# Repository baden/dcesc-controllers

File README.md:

# dcesc-controllers

Тут буде і плата і програма.

## Так. Шось в процесі ми якось дішли до потужної плати. І назва трохи не відповідає.

## Мотори

Експериментую з моторами з редуктором.

Починаю експерімент з [JGA25-370](https://www.aliexpress.com/item/1005006961499514.html)
та [GA24Y-370](https://www.aliexpress.com/item/1005005835525169.html)

на двигунах діаметром 24.4мм

Ціль:
напруга живлення - 24В
струм - 3А
керування - RS485

Хотілось би CAN, але поки не підібрани варіанти конролера.

Пропонується варіанти драйвера двигуна:

- [DRV8870DDAR](https://www.kosmodrom.ua/mikroshema-kontrolera-dviguna/drv8870ddar-4.html) - 12грн
- [DRV8874PWPR](https://www.kosmodrom.ua/mikroshema-kontrolera-dviguna/drv8874pwpr-2.html) - 44грн

# Робимо цю версію на готових драйверах. Бо два-три мотори на одному мікроконтроллері то дуже складно.

## На майбутньє, може буду підбирати якісь китайські компоненти, бо ціна на амеріканських брендах виходить якась зовсім неадекватна.

## Встановлення інструментів

https://github.com/riscv-software-src/homebrew-riscv

```bash
brew tap riscv-software-src/riscv
brew install riscv-tools
brew install riscv-openocd
brew test riscv-tools
/opt/homebrew/opt/riscv-gnu-toolchain/bin/riscv64-unknown-elf-gcc --version
```

/opt/homebrew/opt/riscv-openocd/bin/openocd

## Обираємо мікроконтролер

Я ще не визначився, чи треба робити виключно на CAN, чи може обійтись RS485.

- Оцей мабуть ідеальний для контролеру двигуна
https://www.kosmodrom.ua/mikrokontroler/stm32g431cbt6.html

Для плат с готовий драйвером двигуна, контролер:

https://www.kosmodrom.ua/mikrokontroler/stm32f042f6p6.html

- Шось мегапопулярне, але не впевнен шо воно.
https://www.kosmodrom.ua/mikrokontroler/stm32f103c8t6.html

- Ексотіка для ізвращьєнців
https://www.kosmodrom.ua/mikrokontroler/gd32f103cbt6-2.html

Ще подивлюсь на цей: CH32V203. Здається є сумісний по ногам як STM, так і GD, так і AT

## Обираємо транзистор на потужну плату

### 60 V

https://www.kosmodrom.ua/tranzistor-poloviy-mosfet/60n06-2.html, 39 nC, 14mOhm
https://www.kosmodrom.ua/tranzistor-poloviy-mosfet/csd18537nq5a-2.html, 18 nC, 13mOhm
https://www.kosmodrom.ua/tranzistor-poloviy-mosfet/aon7262e-2.html, 45 nC, 6.2mOhm

## Драйвер MOSFET

https://www.kosmodrom.ua/drayveri-igbt-mosfet/eg3013s-2.html, 0.8/1.0A,

## Драйвер CAN-шини.

Треба або взяти 3.3В CAN, ти живити окремим живленням 5V, та обирати з Vio, чи согласовувати рівні.

https://www.kosmodrom.ua/interfeys-can-2/sn65hvd230dr.html
https://www.kosmodrom.ua/interfeys-can-2/sn65hvd232d.html (no stb and sleep)

## Готовий контролер на слабкіший мотор

https://www.kosmodrom.ua/mikroshema-kontrolera-dviguna/drv8870ddar-4.html, 3.6А, 45V
https://www.kosmodrom.ua/mikroshema-kontrolera-dviguna/drv8870ddar-2.html,
https://www.kosmodrom.ua/mikroshema-kontrolera-dviguna/drv8874pwpr-2.html, 6А, 37V

## Всіляке різне

https://www.kosmodrom.ua/tranzistor-poloviy-mosfet/ao4828.html, дешевий сдвоєний мосфет на драйвер до 3А.

https://www.kosmodrom.ua/stabilizator-naprugi/ht7533s-umw-2.html, Стабілізатор напруги на процесор, 3.3V, 0.1A

## Во, подивиться це

https://github.com/wagiminator/CH32V003-GameConsole/tree/main

Ще це:
https://github.com/wagiminator/MCU-Templates

Ще тут купа посилань:
https://github.com/wagiminator/Development-Boards/tree/main/CH32V003A4M6_DevBoard

https://github.com/AlessandroAU/ESP32-CRSF-Packet-Gen/blob/master/CRSF_testcode/CRSF.h
https://px4.github.io/Firmware-Doxygen/d9/dd2/crsf_8cpp_source.html

https://github.com/vedderb/bldc_uart_comm_stm32f4_discovery/blob/c19a6283e187040f25aa52e213673938db054d06/bldc_interface.c#L567

https://vedder.se/2015/10/communicating-with-the-vesc-using-uart/

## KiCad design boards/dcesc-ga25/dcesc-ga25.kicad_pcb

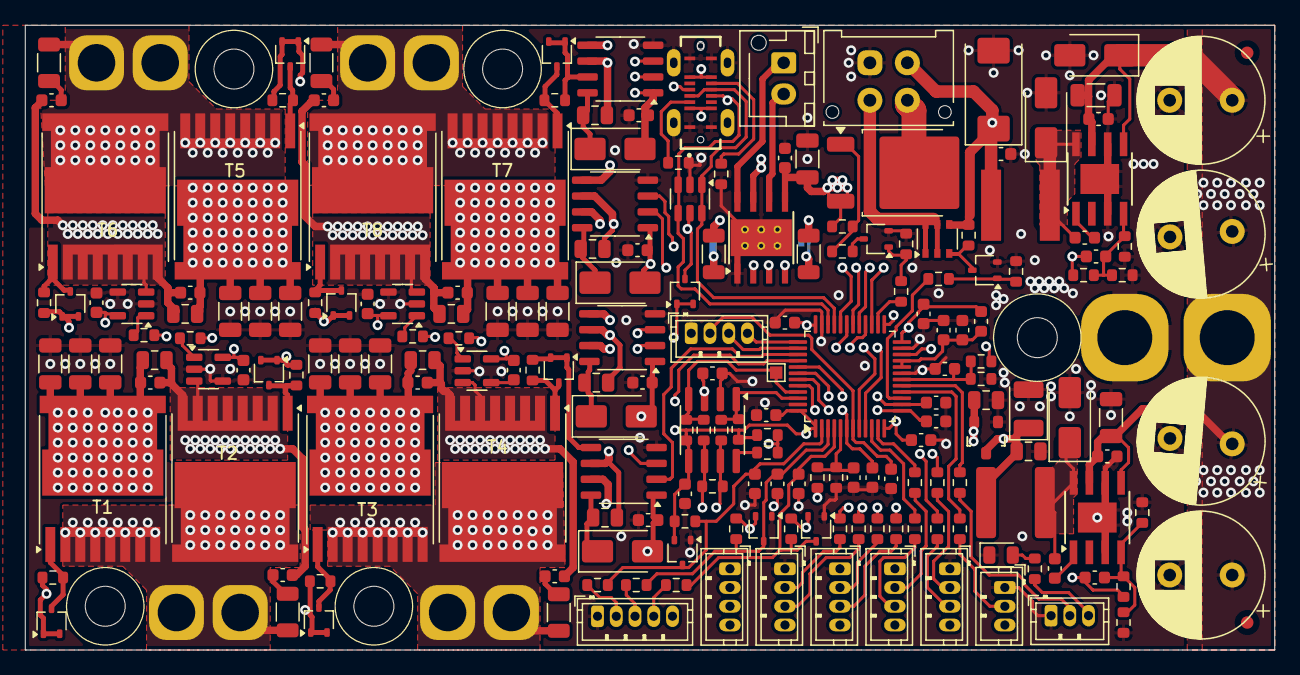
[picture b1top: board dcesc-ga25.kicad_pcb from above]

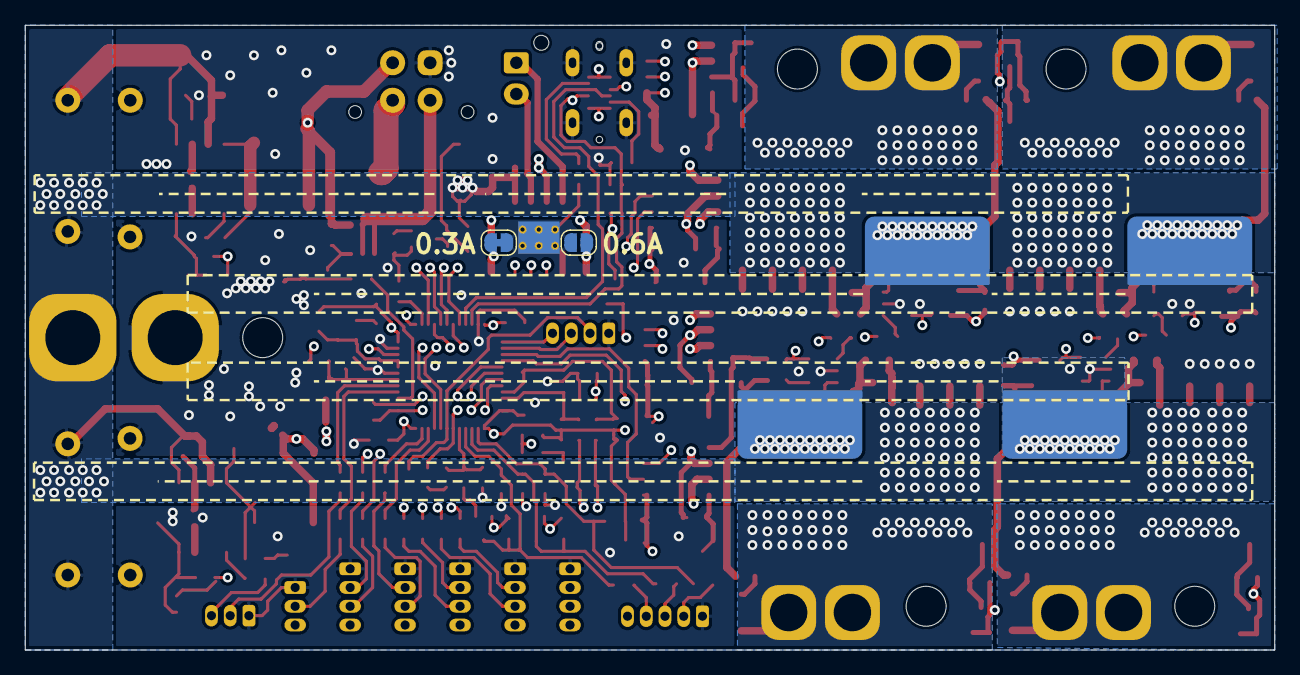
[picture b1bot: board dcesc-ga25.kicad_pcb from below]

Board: 4 copper layers, 100.0 x 50.0 mm, 219 parts (6 on the bottom side), 119 nets.

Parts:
C1, C2, C14, C53, C54, C55, C56, C57, C58, C59, C60, C61, C62, C63, C64: 10uF; C_1206_3216Metric
C3, C4, C5, C6, C10, C15, C16, C17, C18, C19, C20, C21, C25, C27, C28, C29, C30, C31, C32, C33, C34, C35, C36, C37, C38, C39, C40: 0.1uF; C_0603_1608Metric
C7, C8: 82p; C_0603_1608Metric
C9: 100uF; CP_EIA-7343-15_Kemet-W
C11: 100uF; CP_EIA-3528-12_Kemet-T
C12, C13, C45, C46, C47, C48: 10uF; C_0805_2012Metric
C22, C23, C24, C26: 10nF; C_0603_1608Metric
C41, C42, C43, C44: 33nF; C_0603_1608Metric
C49, C50, C51, C52: 1uF; C_0805_2012Metric
C65, C66, C67, C68: 220uF; CP_Radial_D10.0mm_P5.00mm
C69, C70, C71, C72: 3.3nF; C_0603_1608Metric
D1: SMAJ28A; D_SMA
D2, D3, D15, D16, D17, D18: SS24; D_SMA
D4, D5, D6: BAT54SW; SOT-323_SC-70
D7, D8, D9, D10, D11, D12, D13, D14, D19: BAT54AW; SOT-323_SC-70
D20: LED; LED_0805_2012Metric
FB1: FerriteBead; L_0603_1608Metric
FID1, FID2: Fiducial; Fiducial_1mm_Mask2mm
H1, H2, H3, H4, H5: MountingHole; MountingHole_3.2mm_M3
J1: Jumper_2_Open; SolderJumper-2_P1.3mm_Open_RoundedPad1.0x1.5mm
J2: Jumper_2_Bridged; SolderJumper-2_P1.3mm_Bridged_RoundedPad1.0x1.5mm
J3, J4, J5, J6, J7, J8, J9, J10: Conn_01x01_Socket; SolderWire-2.5sqmm_1x01_D2.4mm_OD4.4mm
J18, J19: Conn_01x01_Socket; SolderWire-6sqmm_1x01_D3.5mm_OD7mm
L1, L2: 10uH; Inductor_NR6028T100M
R1, R7, R8, R12, R13, R21, R36: 30k; R_0603_1608Metric
R2, R5, R57: 3.3k; R_0603_1608Metric
R3, R6, R9, R10, R11, R22, R23, R24, R42: 100k; R_0603_1608Metric
R4, R18, R19, R20: 10k; R_0603_1608Metric
R14: 0.51R; R_1206_3216Metric
R15: 1R; R_1206_3216Metric
R16: 120; R_0603_1608Metric
R17, R35: 330k; R_0603_1608Metric
R25, R26, R27, R28, R29, R30, R31, R32, R33, R34, R63, R64: 100; R_0603_1608Metric
R37, R38, R39, R40, R41: 1k; R_0603_1608Metric
R43, R44, R45, R46, R47, R48, R49, R50: 10; R_0603_1608Metric
R51, R52, R53, R54: 3; R_1206_3216Metric
R55, R56, R61, R62: 5.1k; R_0603_1608Metric
R57-1, R58-1, R59-1, R60-1: 0.2mOhm; R_SHUNT
T1, T2, T3, T4, T5, T6, T7, T8: IPT012N08N5; Infineon_PG-HSOF-8-1
T9, T10: BC847AW; SOT-323_SC-70
T11: IRF5803TRPBF; TSOP-6_1.65x3.05mm_P0.95mm
T12: AOD4185; TO-252-2
TP1: BOOT0; TestPoint_Pad_1.0x1.0mm
U1, U2: ST1S14PHR; TI_SO-PowerPAD-8
U3: MCP1703A-3302; MCP1703
U4: STM32G431C8Tx; LQFP-48_7x7mm_P0.5mm
U5, U6, U7, U8: INA180A4; SOT-23-5
U9, U10, U11, U12: EG3112; SOP-8_3.9x4.9mm_P1.27mm
U13: DRV8870DDA; Texas_HTSOP-8-1EP_3.9x4.9mm_P1.27mm_EP2.95x4.9mm_Mask2.4x3.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
U14: ATA6561-GAQW-N; SOIC-8_3.9x4.9mm_P1.27mm
U15: USBLC6-2SC6; SOT-23-6
X1: Conn_02x02_Top_Bottom; Molex_Micro-Fit_3.0_43045-0412_2x02_P3.00mm_Vertical
X2: Conn_01x03; JST_XH_B2B-XH-AM_1x02_P2.50mm_Vertical
X3, X4, X5, X6, X7, X11: Conn_01x03; JST_ZH_B4B-ZR_1x04_P1.50mm_Vertical
X8, X9: Conn_01x03; JST_ZH_B3B-ZR_1x03_P1.50mm_Vertical
X10: Conn_01x03; JST_ZH_B5B-ZR_1x05_P1.50mm_Vertical
X12: USB4120-03-C_REVA; GCT_USB4120-03-C_REVA

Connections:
+3.3V: C13.1, C17.1, C19.1, C20.1, C21.1, C33.1, C34.1, C35.1, C36.1, D4.2 (K), D5.2 (K), D6.2 (K), FB1.2, R22.2, R23.2, R24.2, R42.1, R61.1, R62.1, U3.2 (VO), U4.1 (VBAT), U4.24 (VDD), U4.36 (VDD), U4.48 (VDD), U5.5 (V+), U6.5 (V+), U7.5 (V+), U8.5 (V+), U13.4 (VREF), U14.5 (Vio)
+5V: C8.1, C11.1, C12.1, C16.1, D19.1, D19.2, L2.2, R4.1, R57.1, U3.3 (VI), U14.3 (VDD), X3.4, X4.4, X5.4, X6.4, X8.3, X9.3, X10.5
+12V: C7.1, C9.1, C10.1, C28.1, C29.1, C30.1, C31.1, D15.2 (A), D16.2 (A), D17.2 (A), D18.2 (A), L1.2, R1.1, R11.1, T11.4 (S), U9.1 (VCC), U10.1 (VCC), U11.1 (VCC), U12.1 (VCC), X1.2
+VM: C1.1, C2.1, C3.1, C4.1, C14.1, C15.1, C37.1, C38.1, C39.1, C40.1, C49.1, C50.1, C51.1, C52.1, C53.1, C54.1, C55.1, C56.1, C57.1, C58.1, C59.1, C60.1, C61.1, C62.1, C63.1, C64.1, C65.1, C66.1, C67.1, C68.1, D1.1 (A1), J18.1, R10.1, R17.2, T1.3 (D), T3.3 (D), T5.3 (D), T7.3 (D), T12.3 (S), U1.5 (EN2), U1.7 (VIN), U2.5 (EN2), U2.7 (VIN), U13.5 (VM)
/+12V_ALT: T11.1 (D), T11.2 (D), T11.5 (D), T11.6 (D), X1.3
/+24V_ALT: T12.2 (D), X1.4
/CANH: R16.1, R63.2, U14.7 (CANH), X3.2
/CANL: R16.2, R64.1, U14.6 (CANL), X3.3
/CAN_STBY: R41.2, U14.8 (STBY)
/FDCAN1_RX: R62.2, R64.2, TP1.1, U4.45 (PB8), U14.4 (RXD)
/FDCAN1_TX: R61.2, R63.1, U4.46 (PB9), U14.1 (TXD)
/IC1: C41.1, R37.1, U4.13 (PA5)
/IC2: C42.1, R38.1, U4.12 (PA4)
/IC3: C43.1, R39.1, U4.14 (PA6)
/IC4: C44.1, R40.1, U4.6 (PF1)
/IN1: C24.1, D6.3 (COM), R20.1, R24.1, U4.2 (PC13)
/IN2: C23.1, D5.3 (COM), R19.1, R23.1, U4.3 (PC14)
/IN3: C22.1, D4.3 (COM), R18.1, R22.1, U4.4 (PC15)
/IN_ADC: C27.1, R35.1, R36.1, U4.18 (PB2)
/M1.1/OUT: C45.2, J3.1, J4.1, R51.2, T1.2 (S), T2.3 (D), U9.6 (VS)
/M1.1/PGND: C37.2, C49.2, C69.2, R57-1.1, T2.2 (S), U5.3 (+)
/M1.2/OUT: C46.2, J5.1, J6.1, R52.2, T3.2 (S), T4.3 (D), U10.6 (VS)
/M1.2/PGND: C38.2, C50.2, C70.2, R59-1.1, T4.2 (S), U6.3 (+)
/M1_H: U4.31 (PA9), U9.2 (IN)
/M1_L: U4.28 (PB14), U9.3 (~SD)
/M2.1/OUT: C47.2, J7.1, J8.1, R53.2, T5.2 (S), T6.3 (D), U11.6 (VS)
/M2.1/PGND: C39.2, C51.2, C71.2, R58-1.1, T6.2 (S), U7.3 (+)
/M2.2/OUT: C48.2, J9.1, J10.1, R54.2, T7.2 (S), T8.3 (D), U12.6 (VS)
/M2.2/PGND: C40.2, C52.2, C72.2, R60-1.1, T8.2 (S), U8.3 (+)
/M2_H: U4.39 (PA15), U10.2 (IN)
/M2_L: U4.40 (PB3), U10.3 (~SD)
/M3_H: U4.32 (PA10), U11.2 (IN)
/M3_L: U4.29 (PB15), U11.3 (~SD)
/M4_H: U4.30 (PA8), U12.2 (IN)
/M4_L: U4.27 (PB13), U12.3 (~SD)
/MOT1: U4.9 (PA1), U13.3 (IN1)
/MOT2: U4.8 (PA0), U13.2 (IN2)
/NRST: C32.1, R41.1, R42.2, U4.7 (PG10), X11.2
/P12V: R13.1, U4.15 (PA7)
/P24V: R7.1, U4.26 (PB12)
/PPM1: R27.2, U4.17 (PB1)
/PPM2: R30.2, U4.16 (PB0)
/PPM3: R34.1, U4.41 (PB4)
/PPM4: R33.1, U4.42 (PB5)
/SW1: C5.2, D2.1 (K), L1.1, U1.8 (SW)
/SW2: C6.2, D3.1 (K), L2.1, U2.8 (SW)
/SWCLK: U4.38 (PA14), X11.3
/SWDIO: U4.37 (PA13), X11.4
/USART1_RX: R26.2, U4.44 (PB7)
/USART1_TX: R25.2, U4.43 (PB6)
/USART2_RX: R29.2, U4.11 (PA3)
/USART2_TX: R28.2, U4.10 (PA2)
/USART3_RX: R32.2, U4.25 (PB11)
/USART3_TX: R31.2, U4.22 (PB10)
/USB_DM: U4.34 (PA12), U15.3 (I/O2), U15.4 (I/O2), X12.A7 (D1-), X12.B7 (D2-)
/USB_DP: U4.33 (PA11), U15.1 (I/O1), U15.6 (I/O1), X12.A6 (D1+), X12.B6 (D2+)
/VBUS: D19.3, U15.5 (VBUS), X12.A4 (VBUS_A), X12.A9 (VBUS_A), X12.B4 (VBUS_B), X12.B9 (VBUS_B)
/VDDA: C25.1, C26.1, FB1.1, U4.20 (VREF+), U4.21 (VDDA)
/VOUT: C18.1, R17.1, R21.1, U4.5 (PF0)
GND: C1.2, C2.2, C3.2, C4.2, C9.2, C10.2, C11.2, C12.2, C13.2, C14.2, C15.2, C16.2, C17.2, C18.2, C19.2, C20.2, C21.2, C22.2, C23.2, C24.2, C25.2, C26.2, C27.2, C28.2, C29.2, C30.2, C31.2, C32.2, C33.2, C34.2, C35.2, C36.2, C41.2, C42.2, C43.2, C44.2, C53.2, C54.2, C55.2, C56.2, C57.2, C58.2, C59.2, C60.2, C61.2, C62.2, C63.2, C64.2, C65.2, C66.2, C67.2, C68.2, D1.2 (A2), D2.2 (A), D3.2 (A), D4.1 (A), D5.1 (A), D6.1 (A), D20.1 (K), J1.2 (B), J2.2 (B), J19.1, R2.2, R3.2, R5.2, R6.2, R8.2, R12.2, R21.2, R36.2, R55.2, R56.1, R57-1.2, R58-1.2, R59-1.2, R60-1.2, T9.2 (E), T10.2 (E), U1.3 (~EN1), U1.6 (GND), U1.9 (PADGND), U2.3 (~EN1), U2.6 (GND), U2.9 (PADGND), U3.1 (GND), U4.19 (VSSA), U4.23 (VSS), U4.35 (VSS), U4.47 (VSS), U5.2 (GND), U5.4 (-), U6.2 (GND), U6.4 (-), U7.2 (GND), U7.4 (-), U8.2 (GND), U8.4 (-), U9.4 (COM), U10.4 (COM), U11.4 (COM), U12.4 (COM), U13.1 (GND), U13.9 (GND), U14.2 (VSS), U15.2 (GND), X1.1, X3.1, X4.1, X5.1, X6.1, X7.1, X8.1, X9.1, X10.1, X11.1, X12.A1 (GND_A), X12.A12 (GND_A), X12.B1 (GND_B), X12.B12 (GND_B), X12.S1 (SHIELD), X12.S2 (SHIELD), X12.S3 (SHIELD), X12.S4 (SHIELD)
unnamed: C69.1, R51.1
unnamed: C70.1, R52.1
unnamed: C71.1, R53.1
unnamed: C72.1, R54.1
unnamed: C45.1, D15.1 (K), U9.8 (VB)
unnamed: C46.1, D16.1 (K), U10.8 (VB)
unnamed: C47.1, D17.1 (K), U11.8 (VB)
unnamed: C48.1, D18.1 (K), U12.8 (VB)
unnamed: D20.2 (A), R57.2
unnamed: J1.1 (A), R14.2
unnamed: J2.1 (A), R15.2
unnamed: R37.2, U5.1
unnamed: R38.2, U6.1
unnamed: R39.2, U7.1
unnamed: R40.2, U8.1
unnamed: D7.3, R43.1, T1.1 (G)
unnamed: D8.3, R44.1, T2.1 (G)
unnamed: D9.3, R45.1, T3.1 (G)
unnamed: D10.3, R46.1, T4.1 (G)
unnamed: D11.3, R47.1, T5.1 (G)
unnamed: D12.3, R48.1, T6.1 (G)
unnamed: D13.3, R49.1, T7.1 (G)
unnamed: D14.3, R50.1, T8.1 (G)
unnamed: R12.1, R13.2, T9.1 (B)
unnamed: R7.2, R8.1, T10.1 (B)
unnamed: R9.2, T10.3 (C)
unnamed: R11.2, T9.3 (C), T11.3 (G)
unnamed: R9.1, R10.2, T12.1 (G)
unnamed: C5.1, U1.1 (BOOT)
unnamed: C7.2, R1.2, R2.1, R3.1, U1.4 (FB)
unnamed: C6.1, U2.1 (BOOT)
unnamed: C8.2, R4.2, R5.1, R6.1, U2.4 (FB)
unnamed: D7.1, D7.2, R43.2, U9.7 (HO)
unnamed: D8.1, D8.2, R44.2, U9.5 (LO)
unnamed: D9.1, D9.2, R45.2, U10.7 (HO)
unnamed: D10.1, D10.2, R46.2, U10.5 (LO)
unnamed: D11.1, D11.2, R47.2, U11.7 (HO)
unnamed: D12.1, D12.2, R48.2, U11.5 (LO)
unnamed: D13.1, D13.2, R49.2, U12.7 (HO)
unnamed: D14.1, D14.2, R50.2, U12.5 (LO)
unnamed: R14.1, R15.1, U13.7 (ISEN)
unnamed: U13.6 (OUT1), X2.2
unnamed: U13.8 (OUT2), X2.1
unnamed: R26.1, X4.2
unnamed: R25.1, X4.3
unnamed: R29.1, X5.2
unnamed: R28.1, X5.3
unnamed: R32.1, X6.2
unnamed: R31.1, X6.3
unnamed: R33.2, X7.2
unnamed: R34.2, X7.3
unnamed: R35.2, X7.4
unnamed: R27.1, X8.2
unnamed: R30.1, X9.2
unnamed: R20.2, X10.2
unnamed: R19.2, X10.3
unnamed: R18.2, X10.4
unnamed: R55.1, X12.A5 (CC1)
unnamed: R56.2, X12.B5 (CC2)

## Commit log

2025-07-16 Розведено.
2025-07-16 Плати замовлено.
